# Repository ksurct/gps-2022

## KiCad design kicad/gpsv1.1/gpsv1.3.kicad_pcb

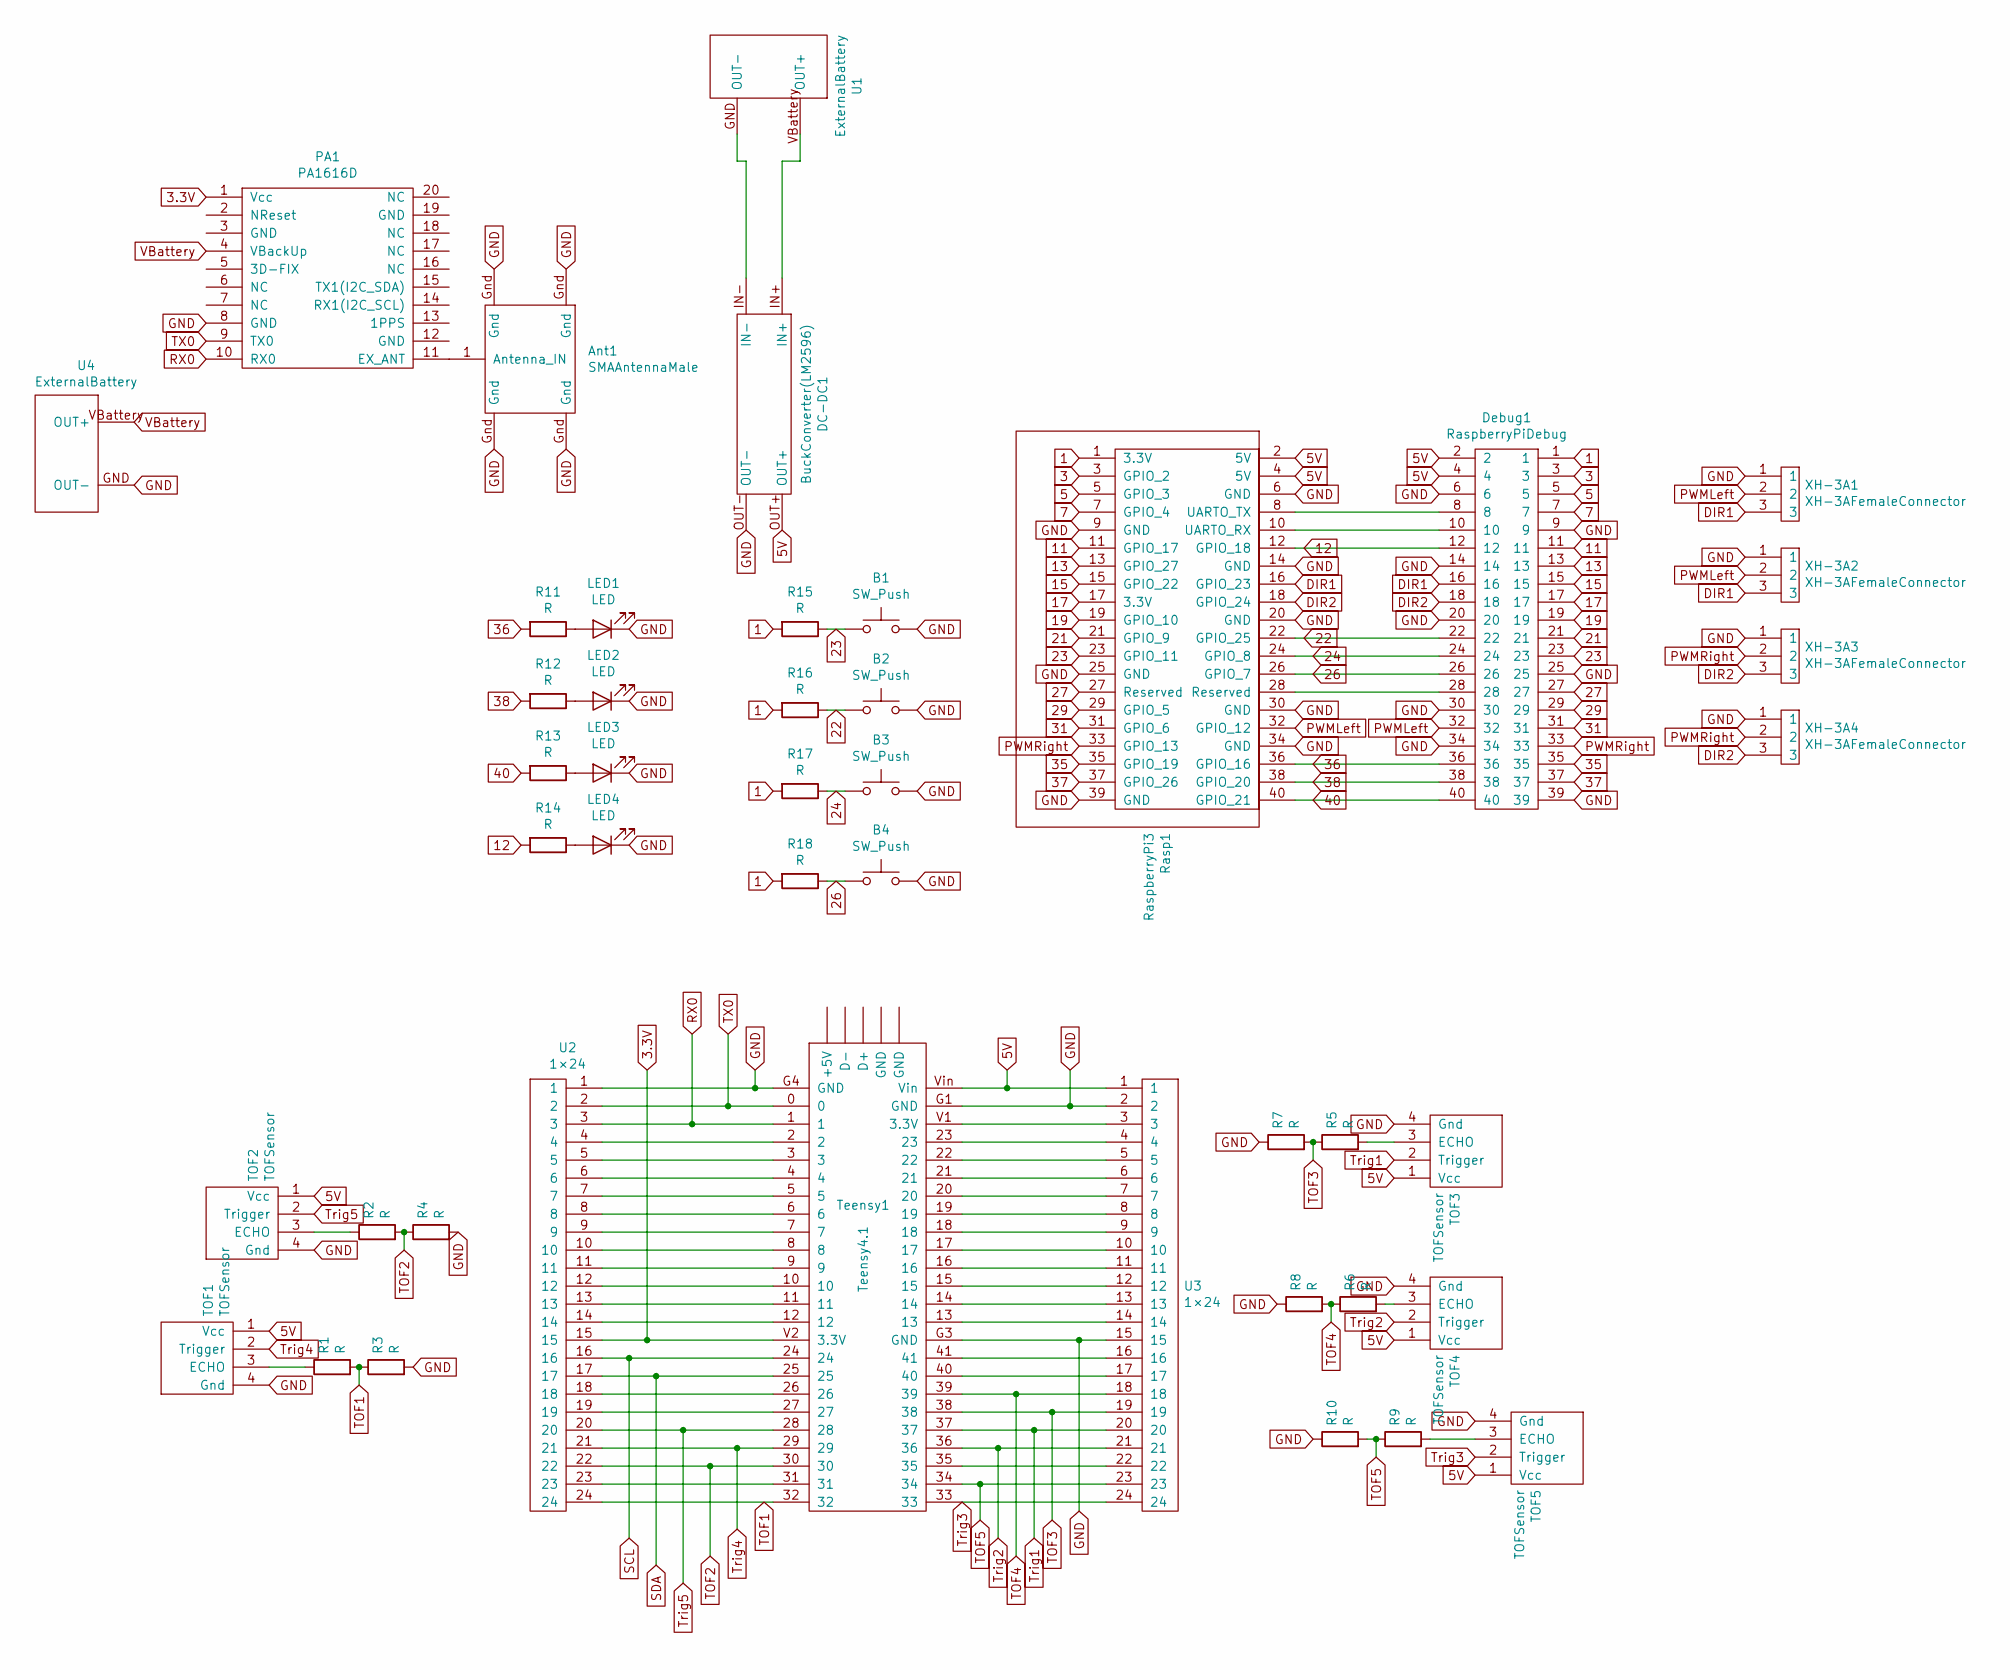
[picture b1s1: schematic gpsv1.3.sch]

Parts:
Ant1: SMAAntennaMale
B1, B2, B3, B4: SW_Push; button
DC-DC1: BuckConverter(LM2596)
Debug1: RaspberryPiDebug; 2×20
LED1, LED2, LED3, LED4: LED; LED_D5.0mm_Clear
PA1: PA1616D; GPS PA1616D
R1, R2, R3, R4, R5, R6, R7, R8, R9, R10, R11, R12, R13, R14, R15, R16, R17, R18: R; Resistor
Rasp1: RaspberryPi3; RasberryPI3
TOF1, TOF2, TOF3, TOF4, TOF5: TOFSensor; TOF Sensor
Teensy1: Teensy4.1; Teensy 4.1
U1: ExternalBattery
U2, U3: 1×24
U4: ExternalBattery; BatteryBackUp
XH-3A1, XH-3A2, XH-3A3, XH-3A4: XH-3AFemaleConnector; XH-3A Female Connector

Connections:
1: Debug1.1, R15.2, R16.2, R17.2, R18.2, Rasp1.1 (3.3V)
3: Debug1.3, Rasp1.3 (GPIO_2)
3.3V: PA1.1 (Vcc), Teensy1.V2 (3.3V), U2.15
5: Debug1.5, Rasp1.5 (GPIO_3)
5V: DC-DC1.OUT+, Debug1.2, Debug1.4, Rasp1.2 (5V), Rasp1.4 (5V), TOF1.1 (Vcc), TOF2.1 (Vcc), TOF3.1 (Vcc), TOF4.1 (Vcc), TOF5.1 (Vcc), Teensy1.Vin, U3.1
7: Debug1.7, Rasp1.7 (GPIO_4)
11: Debug1.11, Rasp1.11 (GPIO_17)
12: Debug1.12, R14.2, Rasp1.12 (GPIO_18)
13: Debug1.13, Rasp1.13 (GPIO_27)
15: Debug1.15, Rasp1.15 (GPIO_22)
17: Debug1.17, Rasp1.17 (3.3V)
19: Debug1.19, Rasp1.19 (GPIO_10)
21: Debug1.21, Rasp1.21 (GPIO_9)
22: B2.1, Debug1.22, R16.1, Rasp1.22 (GPIO_25)
23: B1.1, Debug1.23, R15.1, Rasp1.23 (GPIO_11)
24: B3.1, Debug1.24, R17.1, Rasp1.24 (GPIO_8)
26: B4.1, Debug1.26, R18.1, Rasp1.26 (GPIO_7)
27: Debug1.27, Rasp1.27 (Reserved)
29: Debug1.29, Rasp1.29 (GPIO_5)
31: Debug1.31, Rasp1.31 (GPIO_6)
35: Debug1.35, Rasp1.35 (GPIO_19)
36: Debug1.36, R11.2, Rasp1.36 (GPIO_16)
37: Debug1.37, Rasp1.37 (GPIO_26)
38: Debug1.38, R12.2, Rasp1.38 (GPIO_20)
40: Debug1.40, R13.2, Rasp1.40 (GPIO_21)
DIR1: Debug1.16, Rasp1.16 (GPIO_23), XH-3A1.3, XH-3A2.3
DIR2: Debug1.18, Rasp1.18 (GPIO_24), XH-3A3.3, XH-3A4.3
GND: Ant1.Gnd, B1.2, B2.2, B3.2, B4.2, DC-DC1.OUT-, Debug1.6, Debug1.9, Debug1.14, Debug1.20, Debug1.25, Debug1.30, Debug1.34, Debug1.39, LED1.1 (K), LED2.1 (K), LED3.1 (K), LED4.1 (K), PA1.8 (GND), R3.2, R4.2, R7.1, R8.1, R10.1, Rasp1.6 (GND), Rasp1.9 (GND), Rasp1.14 (GND), Rasp1.20 (GND), Rasp1.25 (GND), Rasp1.30 (GND), Rasp1.34 (GND), Rasp1.39 (GND), TOF1.4 (Gnd), TOF2.4 (Gnd), TOF3.4 (Gnd), TOF4.4 (Gnd), TOF5.4 (Gnd), Teensy1.G1 (GND), Teensy1.G3 (GND), Teensy1.G4 (GND), U2.1, U3.2, U3.15, U4.GND (OUT-), XH-3A1.1, XH-3A2.1, XH-3A3.1, XH-3A4.1
unnamed: Ant1.1 (Antenna_IN), PA1.11 (EX_ANT)
unnamed: DC-DC1.IN+ (‌IN+), U1.VBattery (OUT+)
unnamed: DC-DC1.IN-, U1.GND (OUT-)
unnamed: Debug1.8, Rasp1.8 (UARTO_TX)
unnamed: Debug1.10, Rasp1.10 (UARTO_RX)
unnamed: Debug1.28, Rasp1.28 (Reserved)
unnamed: LED1.2 (A), R11.1
unnamed: LED2.2 (A), R12.1
unnamed: LED3.2 (A), R13.1
unnamed: LED4.2 (A), R14.1
unnamed: R1.1, TOF1.3 (ECHO)
unnamed: R2.1, TOF2.3 (ECHO)
unnamed: R5.2, TOF3.3 (ECHO)
unnamed: R6.2, TOF4.3 (ECHO)
unnamed: R9.2, TOF5.3 (ECHO)
unnamed: Teensy1.2, U2.4
unnamed: Teensy1.3, U2.5
unnamed: Teensy1.4, U2.6
unnamed: Teensy1.5, U2.7
unnamed: Teensy1.6, U2.8
unnamed: Teensy1.7, U2.9
unnamed: Teensy1.8, U2.10
unnamed: Teensy1.9, U2.11
unnamed: Teensy1.10, U2.12
unnamed: Teensy1.11, U2.13
unnamed: Teensy1.12, U2.14
unnamed: Teensy1.13, U3.14
unnamed: Teensy1.14, U3.13
unnamed: Teensy1.15, U3.12
unnamed: Teensy1.16, U3.11
unnamed: Teensy1.17, U3.10
unnamed: Teensy1.18, U3.9
unnamed: Teensy1.19, U3.8
unnamed: Teensy1.20, U3.7
unnamed: Teensy1.21, U3.6
unnamed: Teensy1.22, U3.5
unnamed: Teensy1.23, U3.4
unnamed: Teensy1.26, U2.18
unnamed: Teensy1.27, U2.19
unnamed: Teensy1.31, U2.23
unnamed: Teensy1.35, U3.22
unnamed: Teensy1.40, U3.17
unnamed: Teensy1.41, U3.16
unnamed: Teensy1.V1 (3.3V), U3.3
PWMLeft: Debug1.32, Rasp1.32 (GPIO_12), XH-3A1.2, XH-3A2.2
PWMRight: Debug1.33, Rasp1.33 (GPIO_13), XH-3A3.2, XH-3A4.2
RX0: PA1.10 (RX0), Teensy1.1, U2.3
SCL: Teensy1.24, U2.16
SDA: Teensy1.25, U2.17
TOF1: R1.2, R3.1, Teensy1.32, U2.24
TOF2: R2.2, R4.1, Teensy1.30, U2.22
TOF3: R5.1, R7.2, Teensy1.38, U3.19
TOF4: R6.1, R8.2, Teensy1.39, U3.18
TOF5: R9.1, R10.2, Teensy1.34, U3.23
TX0: PA1.9 (TX0), Teensy1.0, U2.2
Trig1: TOF3.2 (Trigger), Teensy1.37, U3.20
Trig2: TOF4.2 (Trigger), Teensy1.36, U3.21
Trig3: TOF5.2 (Trigger), Teensy1.33, U3.24
Trig4: TOF1.2 (Trigger), Teensy1.29, U2.21
Trig5: TOF2.2 (Trigger), Teensy1.28, U2.20
VBattery: PA1.4 (VBackUp), U4.VBattery (OUT+)

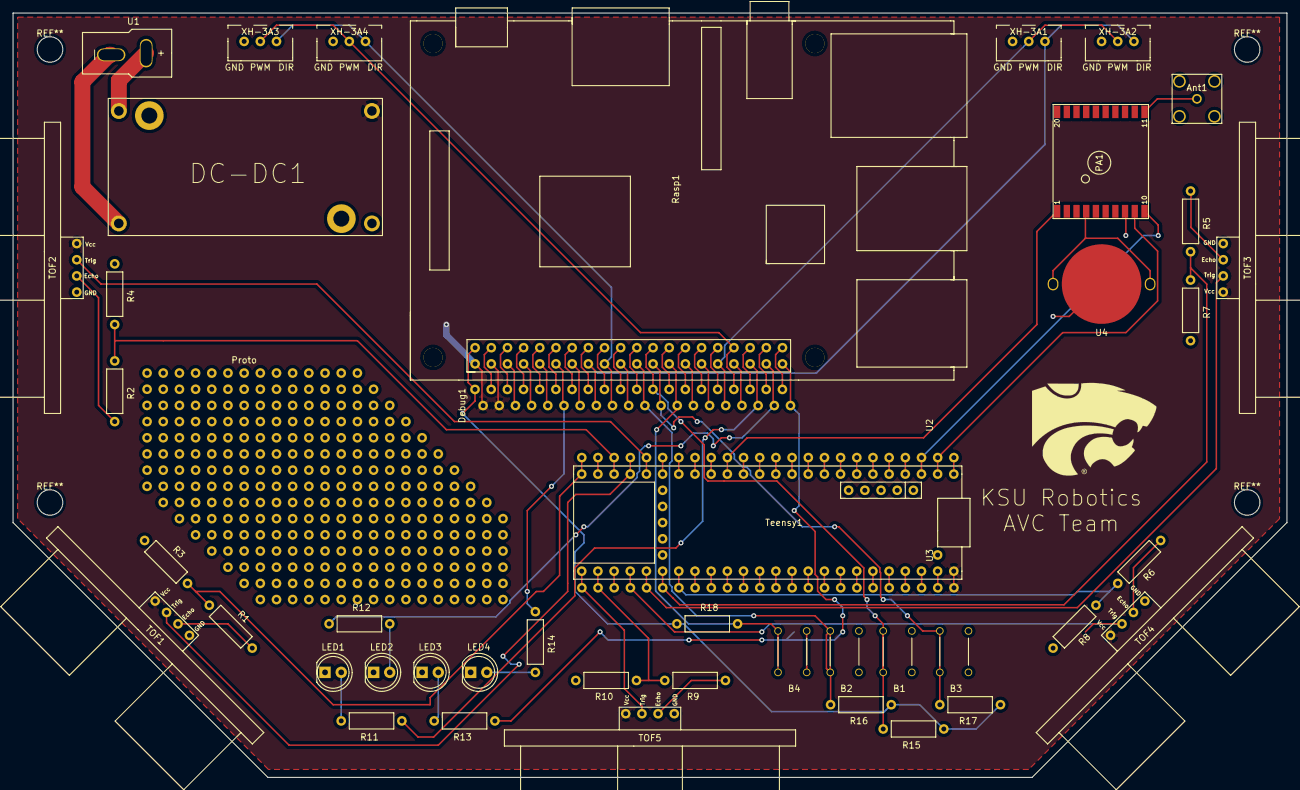
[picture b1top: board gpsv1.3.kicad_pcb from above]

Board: 2 copper layers, 200.0 x 120.0 mm, 46 parts (0 on the bottom side), 89 nets.

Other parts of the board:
Proto: Proto1

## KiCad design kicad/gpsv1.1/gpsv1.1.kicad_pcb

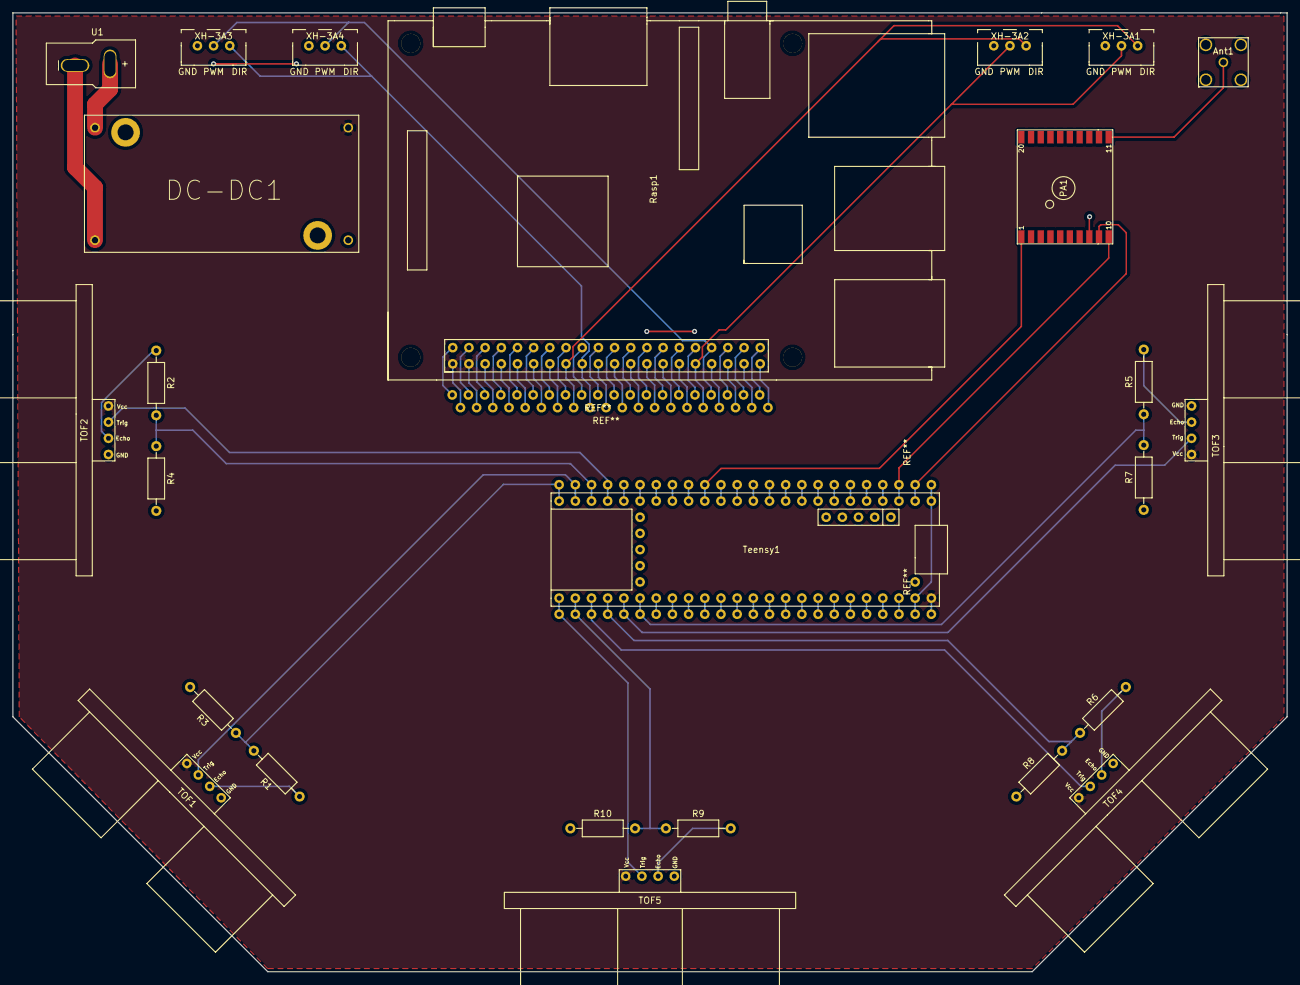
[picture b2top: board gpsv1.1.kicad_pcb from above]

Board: 2 copper layers, 200.0 x 150.5 mm, 25 parts (0 on the bottom side), 26 nets.

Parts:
Ant1: SMAAntennaMale
DC-DC1: BuckConverter(LM2596)
PA1: PA1616D; GPS PA1616D
R1, R2, R3, R4, R5, R6, R7, R8, R9, R10: R; R_Axial_DIN0207_L6.3mm_D2.5mm_P10.16mm_Horizontal
Rasp1: RaspberryPi3; RasberryPI3
TOF1, TOF2, TOF3, TOF4, TOF5: TOFSensor; TOF Sensor
Teensy1: Teensy4.1; Teensy 4.1
U1: ExternalBattery
XH-3A1, XH-3A2, XH-3A3, XH-3A4: XH-3AFemaleConnector; XH-3A Female Connector

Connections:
3.3V: PA1.1, Teensy1.V2
5V: DC-DC1.OUT+, Rasp1.2, Rasp1.4, TOF1.1, TOF2.1, TOF3.1, TOF4.1, TOF5.1, Teensy1.Vin
DIR1: Rasp1.16, XH-3A1.3, XH-3A2.3
DIR2: Rasp1.18, XH-3A3.3, XH-3A4.3
GND: Ant1.Gnd, DC-DC1.OUT-, PA1.8, R3.2, R4.2, R7.1, R8.1, R10.1, Rasp1.6, Rasp1.9, Rasp1.14, Rasp1.20, Rasp1.25, Rasp1.30, Rasp1.34, TOF1.4, TOF2.4, TOF3.4, TOF4.4, TOF5.4, Teensy1.G1, Teensy1.G3, Teensy1.G4, XH-3A1.1, XH-3A2.1, XH-3A3.1, XH-3A4.1
unnamed: Ant1.1, PA1.11
unnamed: DC-DC1.IN+, U1.+
unnamed: R1.1, TOF1.3
unnamed: R1.2, R3.1, Teensy1.32
unnamed: R2.1, TOF2.3
unnamed: R2.2, R4.1, Teensy1.30
unnamed: R5.1, R7.2, Teensy1.38
unnamed: R5.2, TOF3.3
unnamed: R6.1, R8.2, Teensy1.36
unnamed: R6.2, TOF4.3
unnamed: R9.2, TOF5.3
unnamed: R9.1, R10.2, Teensy1.34
PWMLeft: Rasp1.32, XH-3A1.2, XH-3A2.2
PWMRight: Rasp1.33, XH-3A3.2, XH-3A4.2
RX0: PA1.10, Teensy1.1
TX0: PA1.9, Teensy1.0
Trig1: TOF3.2, Teensy1.37
Trig2: TOF4.2, Teensy1.35
Trig3: TOF5.2, Teensy1.33
Trig4: TOF1.2, Teensy1.31
Trig5: TOF2.2, Teensy1.29

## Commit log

2021-10-07 Start of kicad
2021-10-14 Added open cv
2021-10-20 Start of this
2021-10-20 sonic sensor code
2021-10-20 ultra update
2021-10-22 20-21
2021-10-28 Added solid works
    Thanks to Vance
2021-11-03 Made the pcb
2021-11-04 11-3
2021-11-04 Did stuff
2021-11-04 Did more
2021-11-04 Added json
2021-11-04 Format json
2021-11-05 Remove Hall effect
2021-11-05 Added get-pip
2021-11-11 Added Motor insert stl and SW
2021-11-11 new color detection file
2021-11-12 motor class added
2021-11-12 motor test
2021-11-18 11-17
2021-12-01 Done
2021-12-02 Testing my git
2022-01-26 this is the start of the robot simulation
2022-01-26 What was of the chasis
2022-01-28 moved sim from common examples to gps
2022-01-28 left turn
2022-02-02 Made sensors work
2022-02-02 New assebmly
2022-02-02 Got teensy code to output sensor data and maybe gps
2022-02-04 Made the gps data stuff
2022-02-04 Got gps working
2022-02-04 pcb design 3.0
2022-02-08 Small changes to eliminate errors, and added buttons / leds
2022-02-09 modified motor code or something stupid
2022-02-09 Did more solid works
2022-02-10 Made base robot control and added keyboard control exxample
2022-02-11 motor up to date
2022-02-11 added simple input
2022-02-11 update motor/robot
2022-02-11 move robot function
2022-02-11 i :wq git status git status
2022-02-11 somewhat sort have the left distance turn almost working
2022-02-11 constants and rotation code
2022-02-11 Fixed the fork
2022-02-11 idk anymore trying to get serial stuff to work
2022-02-12 finally they can communicate
2022-02-15 made the gearbox
2022-02-16 Ignore this
2022-02-16 adding interrupts but doesnt work
2022-02-16 Turns left and goes in between red barrels then gets stuck
2022-02-17 finally the interupts
2022-02-18 teensy
2022-02-18 working w/ state machine
2022-02-18 Fixed teensy loop
2022-02-24 Made camera work
2022-02-25 sensor and gps data for robot
2022-02-25 leds and buttons
2022-02-26 button stuff
2022-03-02 Updated Simulation
2022-03-02 all together now
2022-03-02 yay its drivable
2022-03-02 Loop and a quarter
2022-03-02 Display this version at the E-Week open house.
2022-03-04 starting algo
2022-03-04 tick
2022-03-04 tick improved
2022-03-04 messed some stuff up then fixed it
2022-03-04 adding dummy algos
2022-03-04 merging stuff
2022-03-04 starting roomba
2022-03-04 janky camera class
2022-03-05 roomba
2022-03-05 more algos
2022-03-09 Created PID algorythym in python to approach a desired angle
2022-03-09 lots of stuff
2022-03-23 PID algo
2022-03-23 accel and mag
2022-03-23 accel and mag pt 2
2022-03-23 Camera is done
2022-03-23 Clean
2022-03-24 Fixed
2022-03-24 Addded dummy algo
2022-03-24 normalizing accel
2022-03-24 iMore
2022-03-24 Did more algop stuff
2022-03-25 sensor data in m instead of cm
2022-03-25 sim with roomba works
2022-03-25 pid sweep
2022-03-25 stuff - Caden
2022-03-25 NOT SURE, FOLLOWING ORDERS TEENSY.INO BOTTOM OF FILE DELAY AND JSON REMOVED
2022-03-25 ouput limits error corrected
2022-03-25 print
2022-03-25 float
2022-03-25 recieve data
2022-03-25 more stuff :)
2022-03-25 i am dumb
2022-03-25 print accel
2022-03-25 iStuff is more
2022-03-25 even more stuff
2022-03-25 annoying stuff
2022-03-25 even more stuff pt 2
2022-03-25 this stuff is getting out of hand
2022-03-25 functionally working but still bugged
2022-03-25 Still buggy but never fails. Will sometimes turn around infront of the ramp go back to the blue barrel, then go back to the ramp and try aggain, will eventually do it successfully
2022-03-25 tried to fix a bug leaving blue, it seems fine, but needs more testinng
2022-03-28 Added camera tuning
2022-03-30 Run py
2022-03-30 slightly less buggy over the ramp
2022-03-30 starting my algo stuff
2022-03-30 small isSim change
2022-03-30 iDon
2022-03-30 resgbl,kuijh
2022-03-30 Revamp of the robot
2022-03-31 rsexd6fiuh
2022-03-31 Added dummy algo
2022-03-31 camera json
2022-03-31 More
2022-03-31 Added
2022-03-31 Close
2022-03-31 camera fixes
2022-03-31 arc rotating
2022-03-31 robot not driving with arc functions
2022-03-31 sim course should be to scale now
2022-03-31 idk more stuff
2022-03-31 algo stuff
2022-04-01 inverted allot of stuff,but it still doesn't work
2022-04-01 done :)
2022-04-01 need to add a correcton for the shorter camera distance, but it is otherwise working
2022-04-02 Added error
2022-04-02 magnetometer
2022-04-02 actually makes it through the whole course clockwise. The pathing could still be optimized
2022-04-02 Did this thing
2022-04-02 Test
2022-04-02 it works, its hard coded, but it works
2022-04-03 magnetometer calibration
2022-04-03 Fixed teensy
2022-04-03 only the red pathing is enabled currently
2022-04-03 only has red pathfinding enabled
2022-04-03 Did something
2022-04-03 Made dum algo
2022-04-03 Made work
2022-04-03 Added and fixed lots
2022-04-03 Starting internet cam
2022-04-03 Update er 1
2022-04-03 made lots
2022-04-03 still only has red enabled, but now has print statements
2022-04-04 Made stuff work
2022-04-04 Can find yellow bucket super consistently
2022-04-04 Made more
2022-04-04 Not bad
2022-04-04 typeamessage
2022-04-04 Push
2022-04-04 magnetometer works
2022-04-04 magnetometer test
2022-04-04 now ready to test
2022-04-04 ted1717
2022-04-05 From pi?
2022-04-05 works again
2022-04-05 test the red with only the camera
2022-04-05 Fixed teds code
2022-04-05 good enough
2022-04-05 TedGoesToBed
2022-04-05 Fixed s f
2022-04-06 Added this thing
2022-04-06 ted224
2022-04-06 ted236
2022-04-06 ted243
2022-04-06 ted422
2022-04-06 ted423
2022-04-06 ted449
2022-04-06 ted458
2022-04-06 Added more
2022-04-06 Course set
2022-04-07 angles
2022-04-07 Made algo work
2022-04-07 comment useless code
2022-04-07 Sensor list
2022-04-07 adding turn method with sensors
2022-04-07 Fixed the sensor functoin
2022-04-07 stuff
2022-04-07 No fancy crap
2022-04-07 goes around
2022-04-08 yay :)
2022-04-08 expand camera
2022-04-08 Added start
2022-04-08 Stop
2022-04-08 guess
2022-04-08 times ratio
2022-04-08 line
2022-04-08 tuned height
2022-04-08 Started object detection only
2022-04-08 Tested outside
2022-04-08 Updated start.py
2022-04-08 Added start up
2022-04-08 Code is coolwq
2022-09-28 7months later
2022-10-26 Change this to work for Mental Health Event.
2022-10-26 stop robot
2022-10-26 added donut and boost
2022-11-02 made a new system for the key presses
2022-11-02 change start speed
2022-11-02 fixes
2022-11-02 Fixed rotation I think
2022-11-10 Possible algorithm for next year's robot
2022-11-30 Add sensors to new algorithm
